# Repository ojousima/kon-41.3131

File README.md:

# kon-41.3131
Aalto university student project for constant temperature controller

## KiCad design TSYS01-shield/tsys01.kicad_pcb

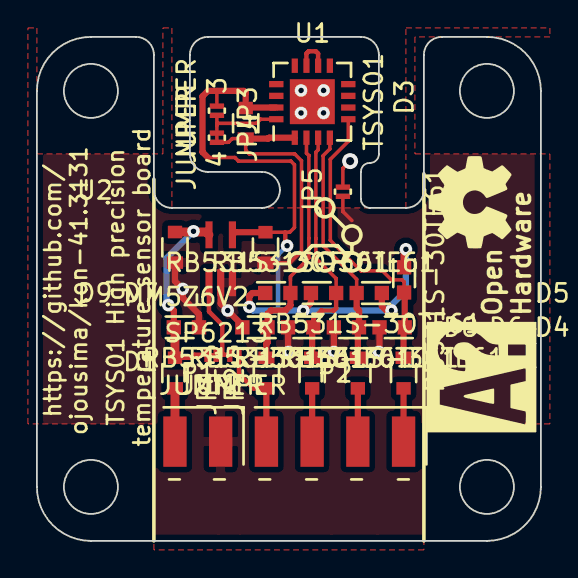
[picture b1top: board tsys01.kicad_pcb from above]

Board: 2 copper layers, 28.0 x 28.0 mm, 26 parts (0 on the bottom side), 14 nets.

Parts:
C1, C2: 2u2; SMD0603_WAVE
C3: 100n; SMD0603_WAVE
D1: MM5Z6V2; SOD-523
D2, D3, D4, D5, D6, D7, D8, D9: RB531S-30TE61; SOD-523
JP1, JP2, JP3, JP4, JP5: JUMPER; R_0201
P1: CONN_01X02; Pin_Header_Angled_SMD_1x02
P2: CONN_01X04; Pin_Header_Angled_SMD_1x04
R1, R2, R3, R4, R5: 220; SMD0603_WAVE
U1: TSYS01; QFN-16-1EP_4x4mm_Pitch0.65mm
U2: SP6213; SC70-6_Handsoldering

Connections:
+3V3: C2.1, C3.1, D3.2, D5.2, D7.2, D9.2, JP3.1, U1.15, U2.4
/CS: JP2.2, P2.4, R2.1
/EN: D8.2, D9.1, R2.2, U1.2
/MISO: P2.1, R5.1
/MOSI: P2.2, R4.1
/PAD: JP5.2, U1.17
/SCLK: P2.3, R3.1
/Vin: C1.1, D1.2, JP1.1, JP1.2, JP2.1, R1.1, U2.1, U2.5
GNDA: C1.2, C2.2, C3.2, D1.1, D2.1, D4.1, D6.1, D8.1, JP3.2, JP4.1, JP4.2, JP5.1, P1.1, U1.1, U1.16, U2.2, U2.3
unnamed: D2.2, D3.1, R5.2, U1.5
unnamed: D4.2, D5.1, R4.2, U1.4
unnamed: D6.2, D7.1, R3.2, U1.3
unnamed: P1.2, R1.2
unnamed: U1.10, U1.11

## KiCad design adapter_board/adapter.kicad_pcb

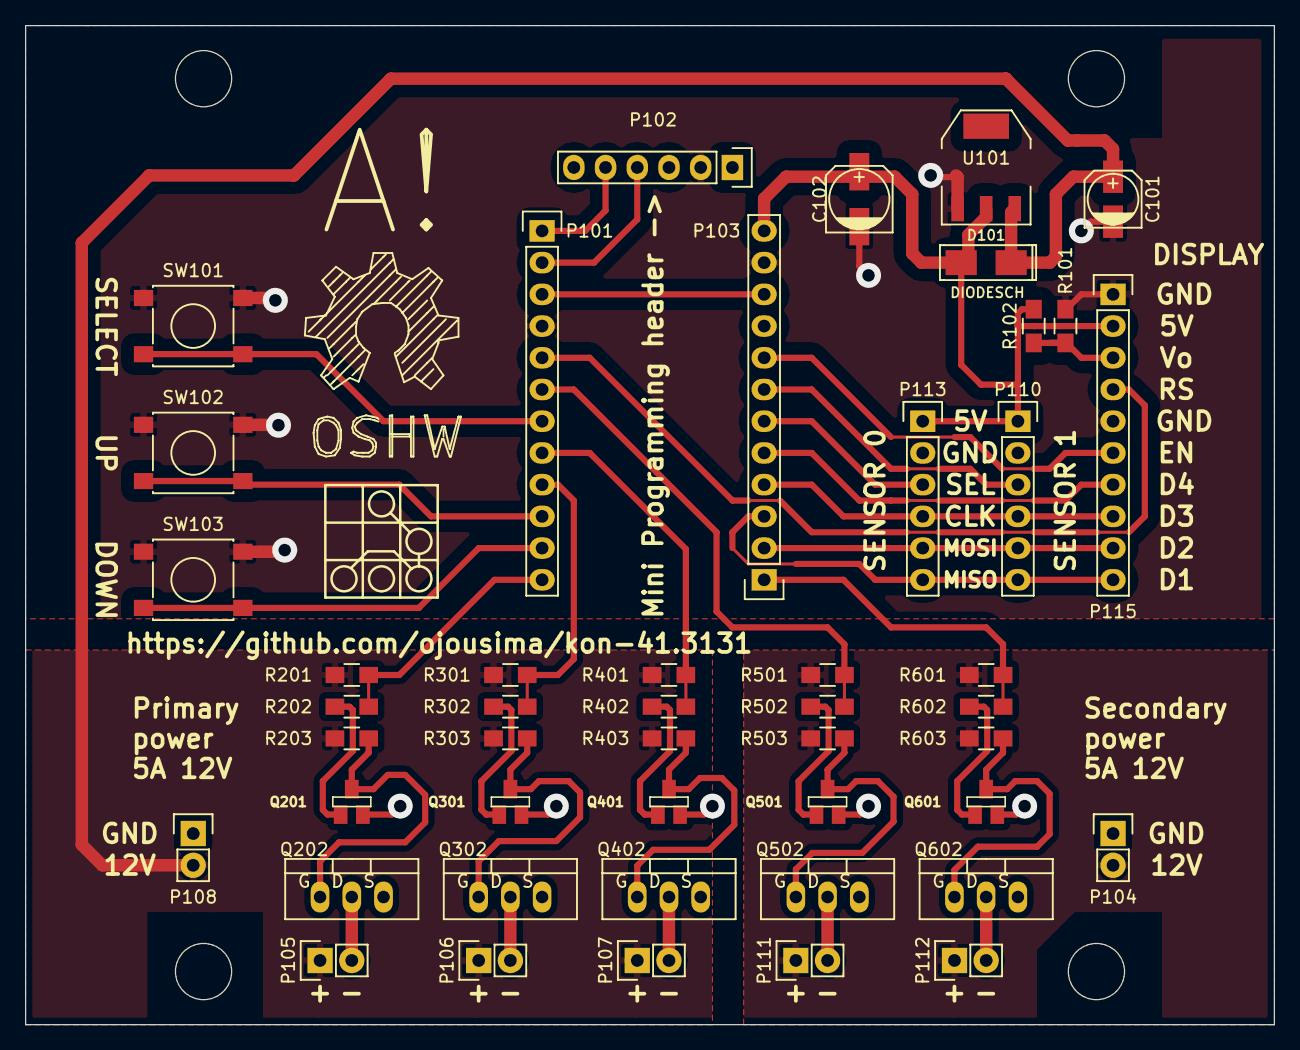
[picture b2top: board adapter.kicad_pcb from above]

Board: 2 copper layers, 100.0 x 80.0 mm, 48 parts (0 on the bottom side), 39 nets.

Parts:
C101: 10u; c_elec_4x5.3
C102: 100u; c_elec_5x5.8
D101: DIODESCH; SMA_WAVE
LOGO101: OPEN_HARDWARE_2; Symbol_OSHW-Logo_SilkScreen_BIG
P101, P103: CONN_01X12; Pin_Header_Straight_1x12
P102, P110, P113: CONN_01X06; Pin_Header_Straight_1x06
P104, P105, P106, P107, P108, P111, P112: CONN_01X02; Pin_Header_Straight_1x02
P115: CONN_01X10; Pin_Header_Straight_1x10
Q201, Q301, Q401, Q501, Q601: BC850; SOT23EBC
Q202, Q302, Q402, Q502, Q602: IRF530N; TO-220_FET-GDS_Vertical
R101, R102: R; R_0805_HandSoldering
R201, R203, R301, R303, R401, R403, R501, R503, R601, R603: 10k; R_0805_HandSoldering
R202, R302, R402, R502, R602: 1k; R_0805_HandSoldering
SW101, SW102, SW103: SPST; SW_SPST_PTS645
U101: LD1117S50TR; SOT-223

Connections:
/5V: C102.1, D101.1, P103.12, P110.1, P113.1, P115.2, R101.1, U101.2
/BT0: P101.7, SW101.2
/BT1: P101.10, SW102.2
/BT2: P101.11, SW103.2
/D4: P103.5, P115.7
/MISO: P103.3, P110.6, P113.6, P115.10
/MOSI: P103.2, P110.5, P113.5, P115.9
/PWM0/12V: C101.1, D101.2, P105.1, P106.1, P107.1, P108.2, R201.1, R203.1, R301.1, R303.1, R401.1, R403.1, U101.3
/PWM0/Drain: P105.2, Q202.D
/PWM0/INV_PWM: P101.12, R201.2, R202.2
/PWM1/Drain: P106.2, Q302.D
/PWM1/INV_PWM: P101.9, R301.2, R302.2
/PWM2/Drain: P107.2, Q402.D
/PWM2/INV_PWM: P101.8, R401.2, R402.2
/PWM3/12V: P104.2, P111.1, P112.1, R501.1, R503.1, R601.1, R603.1
/PWM3/Drain: P111.2, Q502.D
/PWM3/INV_PWM: P101.6, R501.2, R502.2
/PWM4/Drain: P112.2, Q602.D
/PWM4/INV_PWM: P103.1, R601.2, R602.2
/RESET: P101.3, P103.10
/RS: P101.5, P115.4
/RXI: P101.2, P102.4
/SCLK: P103.4, P110.4, P113.4, P115.8
/SEL0: P103.6, P113.3
/SEL1: P103.7, P110.3
/SEL2: P103.8, P115.6
/TXO: P101.1, P102.5
/Vo: P115.3, R101.2, R102.1
GND: C101.2, C102.2, P101.4, P102.2, P103.11, P104.1, P108.1, P110.2, P113.2, P115.1, P115.5, Q201.1, Q202.S, Q301.1, Q302.S, Q401.1, Q402.S, Q501.1, Q502.S, Q601.1, Q602.S, R102.2, SW101.1, SW102.1, SW103.1, U101.1
unnamed: Q201.2, R202.1
unnamed: Q201.3, Q202.G, R203.2
unnamed: Q301.2, R302.1
unnamed: Q301.3, Q302.G, R303.2
unnamed: Q401.2, R402.1
unnamed: Q401.3, Q402.G, R403.2
unnamed: Q501.2, R502.1
unnamed: Q501.3, Q502.G, R503.2
unnamed: Q601.2, R602.1
unnamed: Q601.3, Q602.G, R603.2

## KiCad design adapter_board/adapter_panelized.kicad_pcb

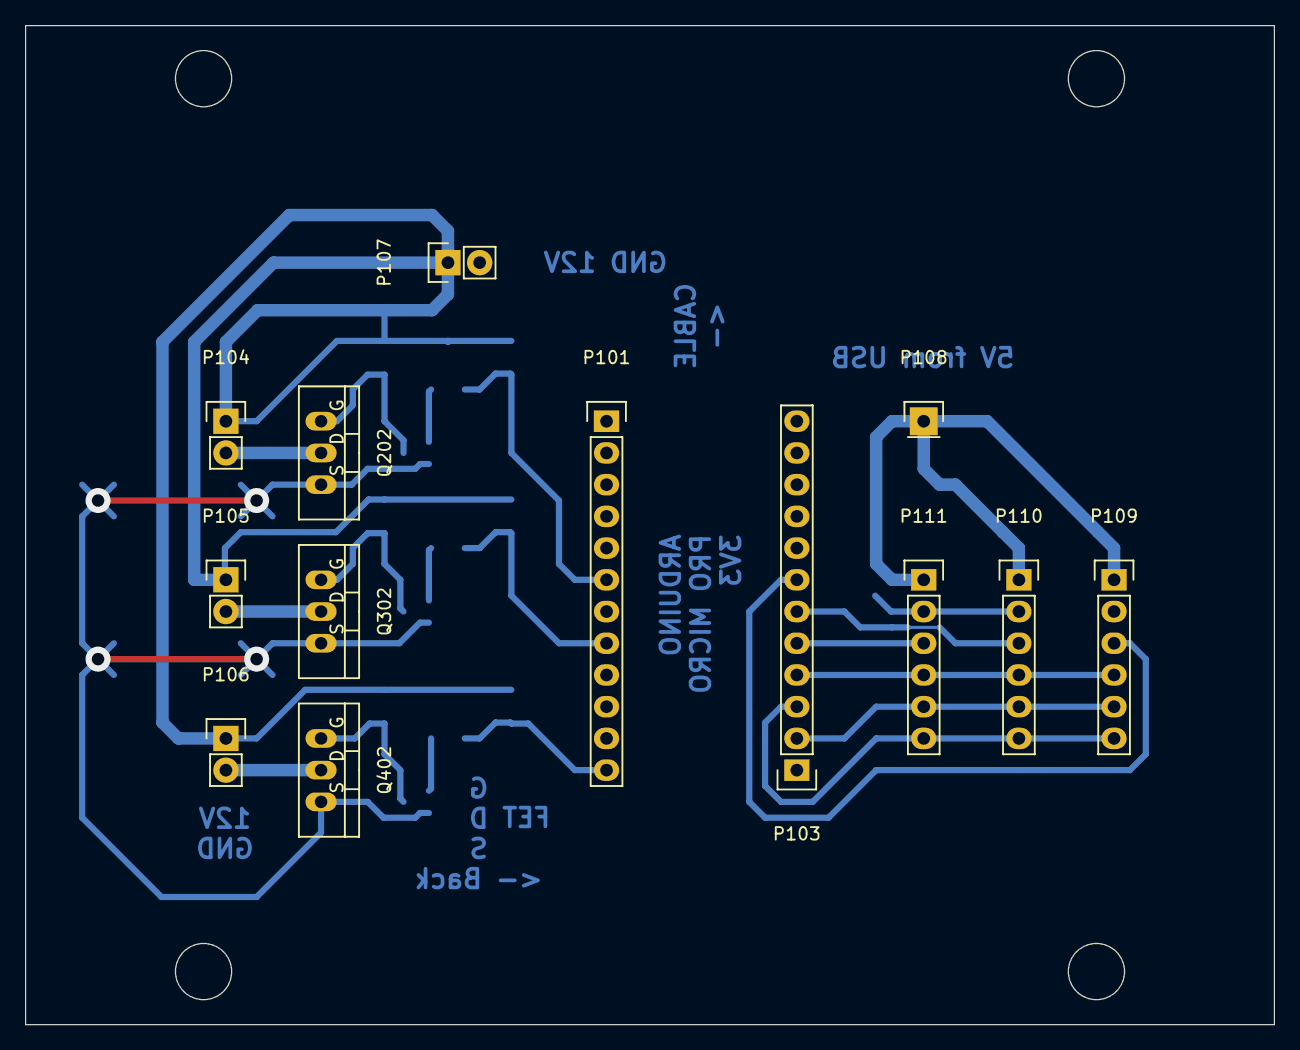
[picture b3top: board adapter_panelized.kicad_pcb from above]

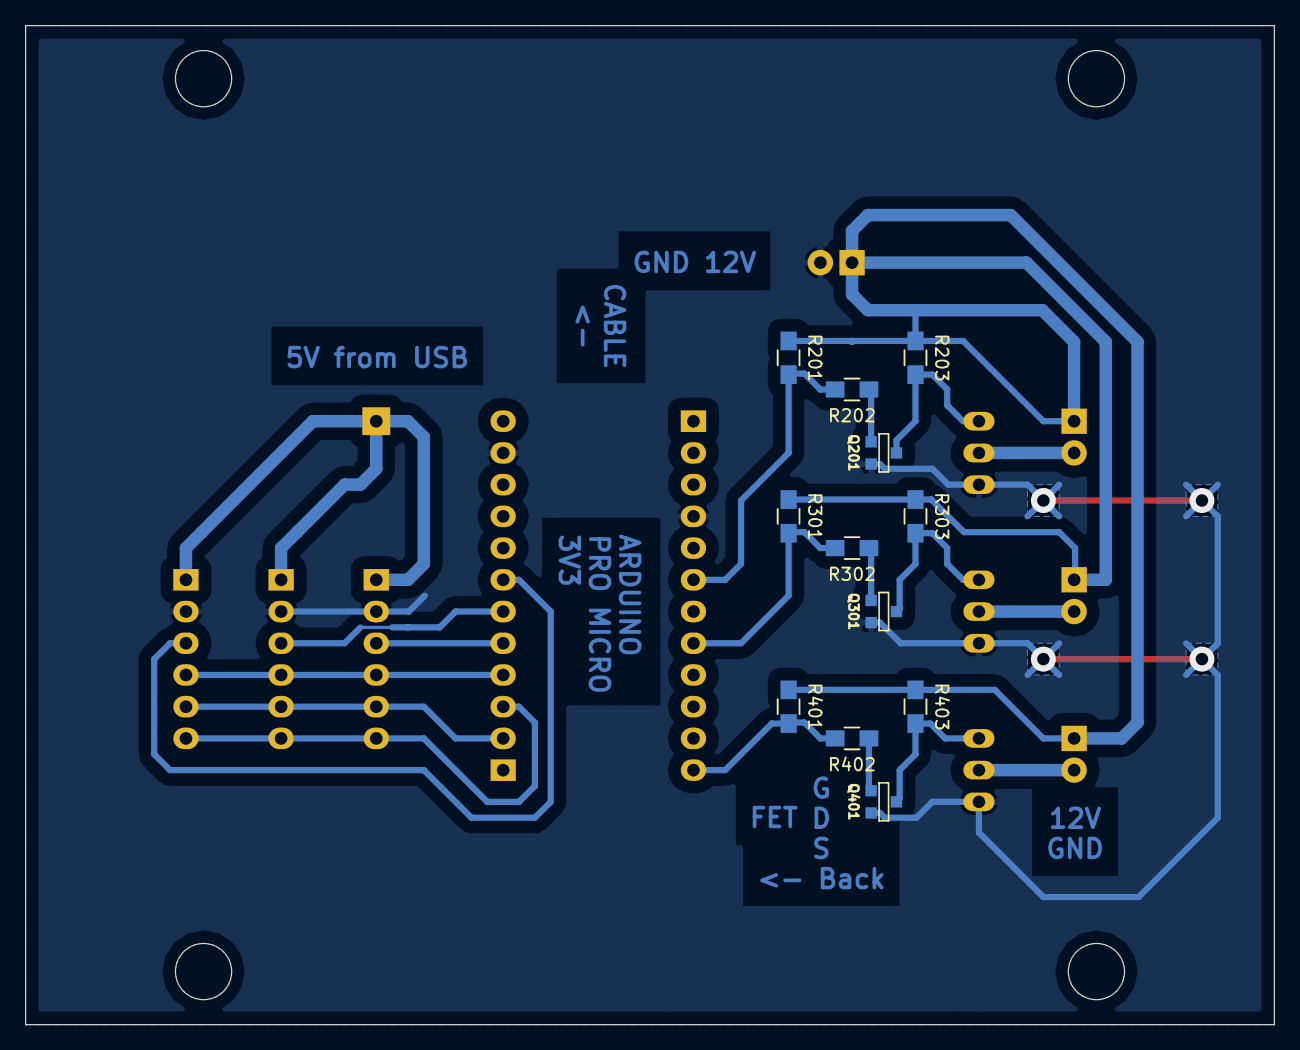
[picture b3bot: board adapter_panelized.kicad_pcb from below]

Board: 2 copper layers, 100.0 x 80.0 mm, 25 parts (12 on the bottom side), 21 nets.

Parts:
P101, P103: CONN_01X12; Pin_Header_Straight_1x12
P104, P105, P106, P107: CONN_01X02; Pin_Header_Straight_1x02
P108: CONN_01X01; Pin_Header_Straight_1x01
P109, P110, P111: CONN_01X06; Pin_Header_Straight_1x06
Q201, Q301, Q401: BC850; SOT23EBC
Q202, Q302, Q402: IRF530N; TO-220_FET-GDS_Vertical
R201, R203, R301, R303, R401, R403: 10k; R_0805_HandSoldering
R202, R302, R402: 1k; R_0805_HandSoldering

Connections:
/5V: P108.1, P109.1, P110.1, P111.1
/MISO: P103.3, P109.6, P110.6, P111.6
/MOSI: P103.2, P109.5, P110.5, P111.5
/PWM0/12V: P104.1, P105.1, P106.1, P107.1, R201.1, R203.1, R301.1, R303.1, R401.1, R403.1
/PWM0/Drain: P104.2, Q202.D
/PWM0/GND: P101.4, P103.11, P107.2, P109.2, P110.2, P111.2, Q201.1, Q202.S, Q301.1, Q302.S, Q401.1, Q402.S
/PWM0/INV_PWM: P101.6, R201.2, R202.2
/PWM1/Drain: P105.2, Q302.D
/PWM1/INV_PWM: P101.8, R301.2, R302.2
/PWM2/Drain: P106.2, Q402.D
/PWM2/INV_PWM: P101.12, R401.2, R402.2
/SCLK: P103.4, P109.4, P110.4, P111.4
/SEL0: P103.5, P111.3
/SEL1: P103.6, P110.3
/SEL2: P103.7, P109.3
unnamed: Q201.2, R202.1
unnamed: Q201.3, Q202.G, R203.2
unnamed: Q301.2, R302.1
unnamed: Q301.3, Q302.G, R303.2
unnamed: Q401.2, R402.1
unnamed: Q401.3, Q402.G, R403.2

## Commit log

2015-01-30 add gedit & kicad backup files to gitignore
2015-01-30 Add first draft of TSYS01 PCB
2015-01-30 add *-bak files to gitignore and fix gedit backup files
2015-02-08 First production version
2015-02-08 Add heater PCB
2015-02-08 Fix jumper connection
2015-02-09 Fix ground of connector
2015-03-23 Fix buffer overflow
    Fixes buffer overflow, calculation is now done correctly. Caveat emptor
    - not tested on real hardware
2015-03-29 First demo version of software
2015-03-29 6 ohm nominal version of heater board
2015-03-29 First version of arduino adapter board
2015-04-01 Add PID control
2015-04-02 Stable model
2015-04-02 Control algorithm stable enough
2015-04-08 Add optimum controller to software
2015-05-05 Add display, 3 pushbuttons, 2 PWM channels
2015-05-31 enlargen pads for handsoldering
2015-07-23 Final version
